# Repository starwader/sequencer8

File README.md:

# sequencer8
Atmega328P based CV sequencer

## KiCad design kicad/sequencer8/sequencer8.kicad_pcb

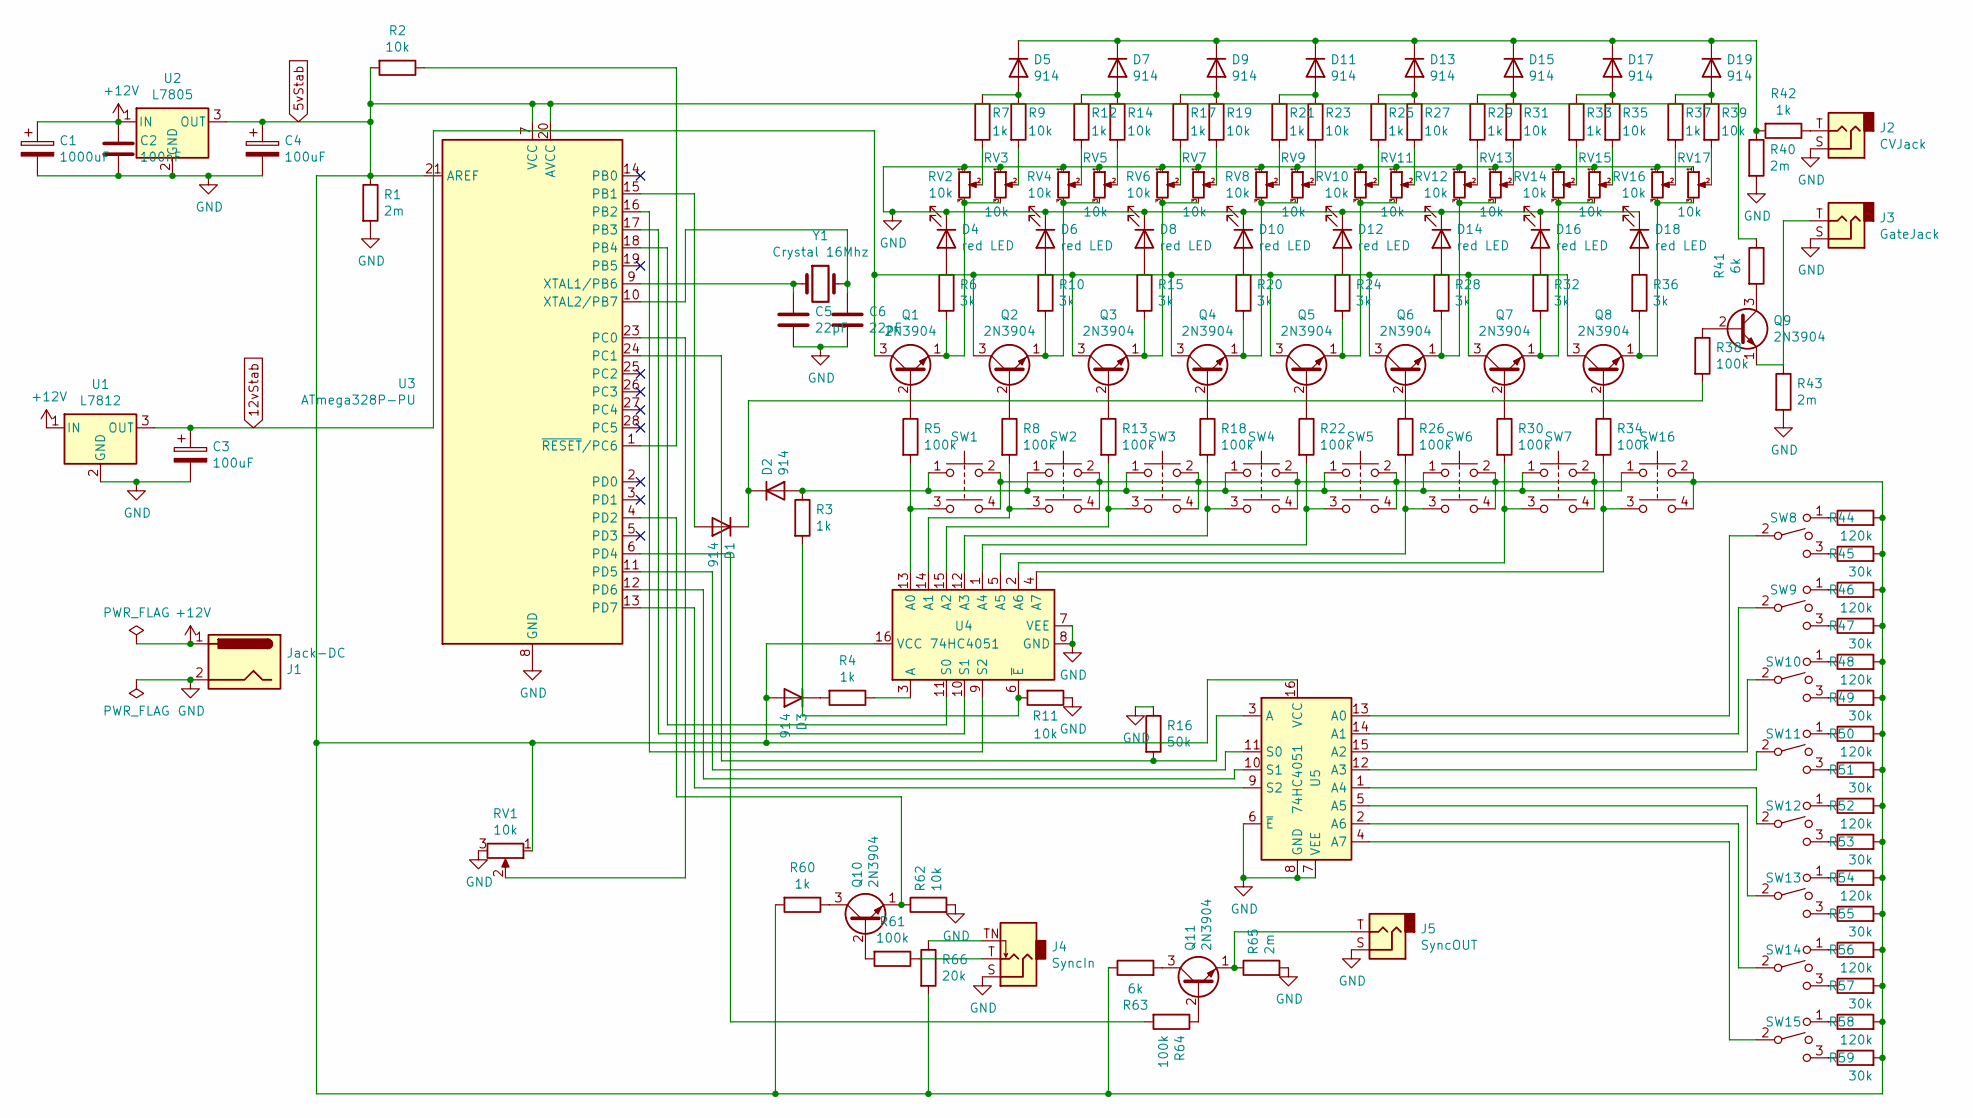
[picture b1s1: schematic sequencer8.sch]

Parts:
C1: 1000uF; CP_Radial_D10.0mm_P2.50mm
C2: 100nF; C_Rect_L7.2mm_W2.5mm_P5.00mm_FKS2_FKP2_MKS2_MKP2
C3, C4: 100uF; CP_Radial_D6.3mm_P2.50mm
C5, C6: 22pF; C_Disc_D5.0mm_W2.5mm_P2.50mm
D1, D2, D3, D5, D7, D9, D11, D13, D15, D17, D19: 914; D_A-405_P7.62mm_Horizontal
D4, D6, D8, D10, D12, D14, D16, D18: red LED; LED_D5.0mm
J1: Jack-DC; BarrelJack_Horizontal
J2: CVJack; Jack_3.5mm_QingPu_WQP-PJ398SM_Vertical_CircularHoles
J3: GateJack; Jack_3.5mm_QingPu_WQP-PJ398SM_Vertical_CircularHoles
J4: SyncIn; Jack_3.5mm_QingPu_WQP-PJ398SM_Vertical_CircularHoles
J5: SyncOUT; Jack_3.5mm_QingPu_WQP-PJ398SM_Vertical_CircularHoles
Q1, Q2, Q3, Q4, Q5, Q6, Q7, Q8, Q9, Q10, Q11: 2N3904; TO-92_Inline
R1, R40, R43, R65: 2m; R_Axial_DIN0207_L6.3mm_D2.5mm_P7.62mm_Horizontal
R2, R9, R11, R14, R19, R23, R27, R31, R35, R39, R62: 10k; R_Axial_DIN0207_L6.3mm_D2.5mm_P7.62mm_Horizontal
R3, R4, R7, R12, R17, R21, R25, R29, R33, R37, R42, R60: 1k; R_Axial_DIN0207_L6.3mm_D2.5mm_P7.62mm_Horizontal
R5, R8, R13, R18, R22, R26, R30, R34, R38, R61, R64: 100k; R_Axial_DIN0207_L6.3mm_D2.5mm_P7.62mm_Horizontal
R6, R10, R15, R20, R24, R28, R32, R36: 3k; R_Axial_DIN0207_L6.3mm_D2.5mm_P7.62mm_Horizontal
R16: 50k; R_Axial_DIN0207_L6.3mm_D2.5mm_P7.62mm_Horizontal
R41, R63: 6k; R_Axial_DIN0207_L6.3mm_D2.5mm_P7.62mm_Horizontal
R44, R46, R48, R50, R52, R54, R56, R58: 120k; R_Axial_DIN0207_L6.3mm_D2.5mm_P7.62mm_Horizontal
R45, R47, R49, R51, R53, R55, R57, R59: 30k; R_Axial_DIN0207_L6.3mm_D2.5mm_P7.62mm_Horizontal
R66: 20k; R_Axial_DIN0207_L6.3mm_D2.5mm_P7.62mm_Horizontal
RV1, RV2, RV3, RV4, RV5, RV6, RV7, RV8, RV9, RV10, RV11, RV12, RV13, RV14, RV15, RV16, RV17: 10k; Potentiometer_Alps_RK09L_Single_Vertical
SW1, SW2, SW3, SW4, SW5, SW6, SW7, SW16: SW_Push_Dual; SW_PUSH-12mm_Wuerth-430476085716
SW8, SW9, SW10, SW11, SW12, SW13, SW14, SW15: SW_SPDT_MSM; switch_100sp5
U1: L7812; TO-92_Inline
U2: L7805; TO-92_Inline
U3: ATmega328P-PU; DIP-28_W7.62mm
U4, U5: 74HC4051; DIP-16_W7.62mm
Y1: Crystal 16Mhz; Crystal_HC49-4H_Vertical

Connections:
5vStab: C4.1, D3.2 (A), R1.1, R2.2, R41.1, R44.2, R45.2, R46.2, R47.2, R48.2, R49.2, R50.2, R51.2, R52.2, R53.2, R54.2, R55.2, R56.2, R57.2, R58.2, R59.2, R60.2, R63.1, R66.2, RV1.1, SW1.2, SW1.4, SW2.2, SW2.4, SW3.2, SW3.4, SW4.2, SW4.4, SW5.2, SW5.4, SW6.2, SW6.4, SW7.2, SW7.4, SW16.2, SW16.4, U2.3 (OUT), U3.7 (VCC), U3.20 (AVCC), U3.21 (AREF), U4.16 (VCC), U5.16 (VCC)
12vStab: C3.1, Q1.3 (C), Q2.3 (C), Q3.3 (C), Q4.3 (C), Q5.3 (C), Q6.3 (C), Q7.3 (C), Q8.3 (C), U1.3 (OUT)
+12V: C1.1, C2.1, J1.1, U1.1 (IN), U2.1 (IN)
GND: C1.2, C2.2, C3.2, C4.2, C5.2, C6.2, D4.1 (K), D6.1 (K), D8.1 (K), D10.1 (K), D12.1 (K), D14.1 (K), D16.1 (K), D18.1 (K), J1.2, J2.S, J3.S, J4.S, J5.S, R1.2, R11.1, R16.1, R40.2, R43.2, R62.2, R65.2, RV1.3, RV2.1, RV3.1, RV4.1, RV5.1, RV6.1, RV7.1, RV8.1, RV9.1, RV10.1, RV11.1, RV12.1, RV13.1, RV14.1, RV15.1, RV16.1, RV17.1, U1.2 (GND), U2.2 (GND), U3.8 (GND), U3.22 (GND), U4.7 (VEE), U4.8 (GND), U5.6 (~E), U5.7 (VEE), U5.8 (GND)
unnamed: C5.1, U3.9 (XTAL1/PB6), Y1.1
unnamed: C6.1, U3.10 (XTAL2/PB7), Y1.2
unnamed: D1.1 (K), D2.1 (K), R38.2
unnamed: D1.2 (A), U3.15 (PB1)
unnamed: D2.2 (A), R3.1, SW1.1, SW2.1, SW3.1, SW4.1, SW5.1, SW6.1, SW7.1, SW16.1
unnamed: D3.1 (K), R4.2
unnamed: D4.2 (A), R6.1
unnamed: D5.2 (A), R7.1, R9.1
unnamed: D6.2 (A), R10.1
unnamed: D7.2 (A), R12.1, R14.1
unnamed: D8.2 (A), R15.1
unnamed: D9.2 (A), R17.1, R19.1
unnamed: D10.2 (A), R20.1
unnamed: D5.1 (K), D7.1 (K), D9.1 (K), D11.1 (K), D13.1 (K), D15.1 (K), D17.1 (K), D19.1 (K), R40.1, R42.2
unnamed: D11.2 (A), R21.1, R23.1
unnamed: D12.2 (A), R24.1
unnamed: D13.2 (A), R25.1, R27.1
unnamed: D14.2 (A), R28.1
unnamed: D15.2 (A), R29.1, R31.1
unnamed: D16.2 (A), R32.1
unnamed: D17.2 (A), R33.1, R35.1
unnamed: D18.2 (A), R36.1
unnamed: D19.2 (A), R37.1, R39.1
unnamed: J2.T, R42.1
unnamed: J3.T, Q9.1 (E), R43.1
unnamed: J4.T, R61.1
unnamed: J4.TN, R66.1
unnamed: J5.T, Q11.1 (E), R65.1
unnamed: Q1.1 (E), R6.2, RV2.3, RV3.3
unnamed: Q1.2 (B), R5.1
unnamed: Q2.1 (E), R10.2, RV4.3, RV5.3
unnamed: Q2.2 (B), R8.1
unnamed: Q3.1 (E), R15.2, RV6.3, RV7.3
unnamed: Q3.2 (B), R13.1
unnamed: Q4.1 (E), R20.2, RV8.3, RV9.3
unnamed: Q4.2 (B), R18.1
unnamed: Q5.1 (E), R24.2, RV10.3, RV11.3
unnamed: Q5.2 (B), R22.1
unnamed: Q6.1 (E), R28.2, RV12.3, RV13.3
unnamed: Q6.2 (B), R26.1
unnamed: Q7.1 (E), R32.2, RV14.3, RV15.3
unnamed: Q7.2 (B), R30.1
unnamed: Q8.1 (E), R36.2, RV16.3, RV17.3
unnamed: Q8.2 (B), R34.1
unnamed: Q9.2 (B), R38.1
unnamed: Q9.3 (C), R41.2
unnamed: Q10.1 (E), R62.1, U3.4 (PD2)
unnamed: Q10.2 (B), R61.2
unnamed: Q10.3 (C), R60.1
unnamed: Q11.2 (B), R64.1
unnamed: Q11.3 (C), R63.2
unnamed: R2.1, U3.1 (~RESET~/PC6)
unnamed: R4.1, U4.3 (A)
unnamed: R5.2, SW1.3, U4.13 (A0)
unnamed: R7.2, RV2.2
unnamed: R8.2, SW2.3, U4.14 (A1)
unnamed: R9.2, RV3.2
unnamed: R3.2, R11.2, U4.6 (~E)
unnamed: R12.2, RV4.2
unnamed: R13.2, SW3.3, U4.15 (A2)
unnamed: R14.2, RV5.2
unnamed: R16.2, U3.24 (PC1), U5.3 (A)
unnamed: R17.2, RV6.2
unnamed: R18.2, SW4.3, U4.12 (A3)
unnamed: R19.2, RV7.2
unnamed: R21.2, RV8.2
unnamed: R22.2, SW5.3, U4.1 (A4)
unnamed: R23.2, RV9.2
unnamed: R25.2, RV10.2
unnamed: R26.2, SW6.3, U4.5 (A5)
unnamed: R27.2, RV11.2
unnamed: R29.2, RV12.2
unnamed: R30.2, SW7.3, U4.2 (A6)
unnamed: R31.2, RV13.2
unnamed: R33.2, RV14.2
unnamed: R34.2, SW16.3, U4.4 (A7)
unnamed: R35.2, RV15.2
unnamed: R37.2, RV16.2
unnamed: R39.2, RV17.2
unnamed: R44.1, SW8.1
unnamed: R45.1, SW8.3
unnamed: R46.1, SW9.1
unnamed: R47.1, SW9.3
unnamed: R48.1, SW10.1
unnamed: R49.1, SW10.3
unnamed: R50.1, SW11.1
unnamed: R51.1, SW11.3
unnamed: R52.1, SW12.1
unnamed: R53.1, SW12.3
unnamed: R54.1, SW13.1
unnamed: R55.1, SW13.3
unnamed: R56.1, SW14.1
unnamed: R57.1, SW14.3
unnamed: R58.1, SW15.1
unnamed: R59.1, SW15.3
unnamed: R64.2, U3.6 (PD4)
unnamed: RV1.2, U3.23 (PC0)
unnamed: SW8.2, U5.13 (A0)
unnamed: SW9.2, U5.14 (A1)
unnamed: SW10.2, U5.15 (A2)
unnamed: SW11.2, U5.12 (A3)
unnamed: SW12.2, U5.1 (A4)
unnamed: SW13.2, U5.5 (A5)
unnamed: SW14.2, U5.2 (A6)
unnamed: SW15.2, U5.4 (A7)
unnamed: U3.11 (PD5), U5.11 (S0)
unnamed: U3.12 (PD6), U5.10 (S1)
unnamed: U3.13 (PD7), U5.9 (S2)
unnamed: U3.16 (PB2), U4.9 (S2)
unnamed: U3.17 (PB3), U4.10 (S1)
unnamed: U3.18 (PB4), U4.11 (S0)

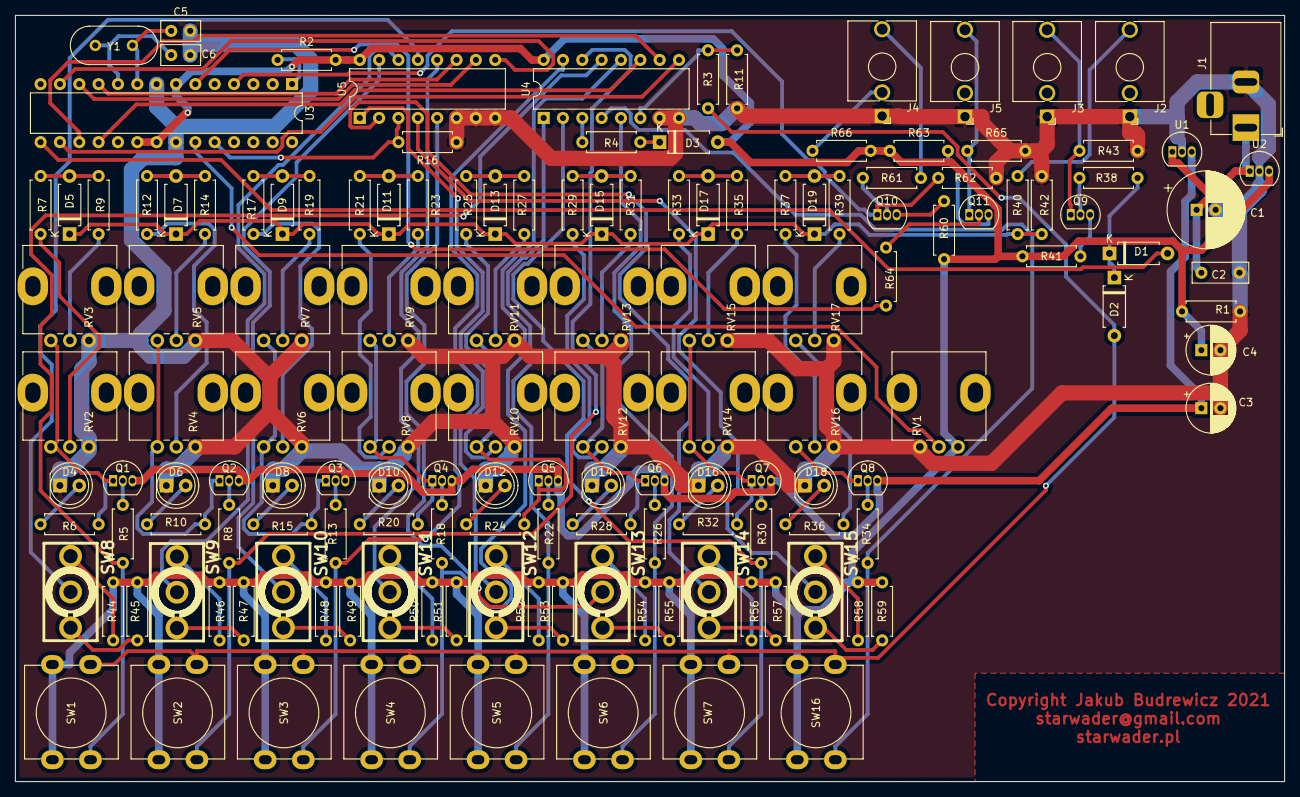
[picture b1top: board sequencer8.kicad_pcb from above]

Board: 2 copper layers, 166.6 x 100.6 mm, 146 parts (0 on the bottom side), 115 nets.

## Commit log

2021-07-16 initial
2021-07-16 add pcb 3d view

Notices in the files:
kicad/sequencer8/sequencer8.kicad_pcb:
Copyright Jakub Budrewicz 2021
